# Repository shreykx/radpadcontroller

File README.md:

**radpad** - radpad is supposed to be a simple hackpad built on the radiation spider theme for [hackclub](https://hackclub.com) [#fallen](https://fallen.hackclub.com). the idea is, a macrocontroller that allows you to navigate your computer interface more easily than before. i will be documenting the progress on official fallout slack channel, and everything at source goes here :)

**for the reviewer**

**pcb schematic** - showing all the logical connections that will go into radpad's circuit. i've used in total three main electrical components, the com model joystick (it has both x and y directions plus a push button for center), four sw_switch for push buttons and a XIAO microcontroller.  

**pcb design** - i just connected the ratsnests to form a basic design, using both f.cu and b.cu layers making my board a 2 layered one.

3d front

3d back

i'm basically using the kicad's inbuilt 3d viewer to view how my board will look like at the end. which will decide if it works. i've also noted down the dimensions so the case is printed accordingly.

**3d model**

* software used: onshape

the base model is an imported one, which i will customize to fit radpad's theme. also there are a few layout shifts done.

i will upload more photos as i progress and also of the real ones after parts assembly.

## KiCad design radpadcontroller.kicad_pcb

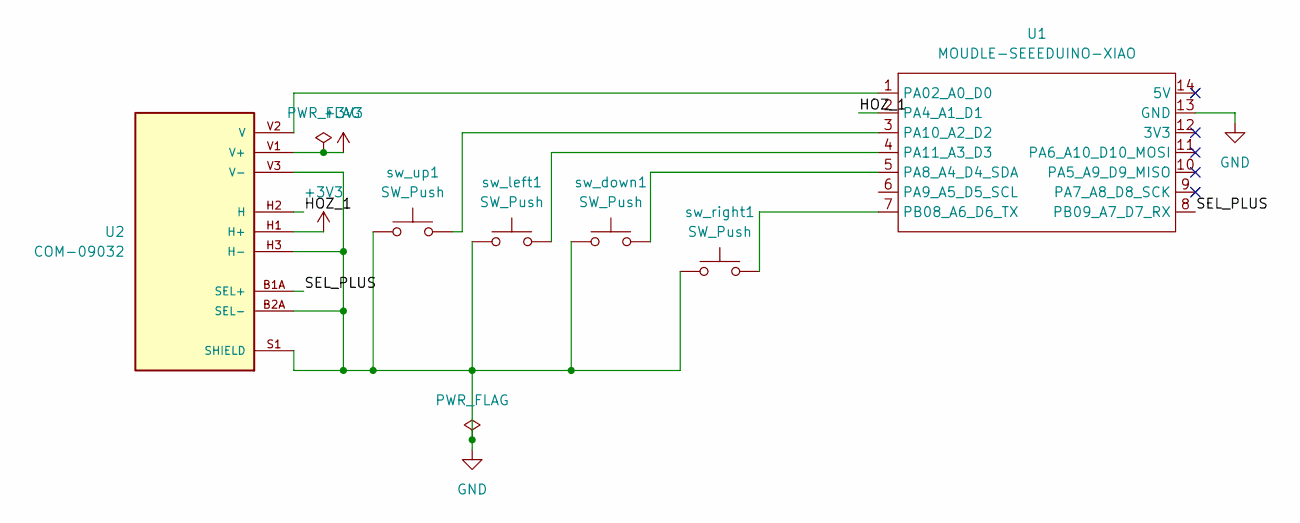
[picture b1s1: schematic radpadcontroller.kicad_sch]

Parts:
U1: MOUDLE-SEEEDUINO-XIAO; XIAO-Generic-Hybrid-14P-2.54-21X17.8MM
U2: COM-09032; XDCR_COM-09032; MPN COM-09032
sw_down1: SW_Push; SW_PUSH_6mm
sw_left1: SW_Push; SW_PUSH_6mm
sw_right1: SW_Push; SW_PUSH_6mm
sw_up1: SW_Push; SW_PUSH_6mm

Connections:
+3V3: U2.H1 (H+), U2.V1 (V+)
/HOZ_1: U1.2 (PA4_A1_D1), U2.H2 (H)
/SEL_PLUS: U1.8 (PB09_A7_D7_RX), U2.B1A (SEL+)
GND: U1.13 (GND), U2.B2A (SEL-), U2.H3 (H-), U2.S1 (SHIELD), U2.S2 (SHIELD), U2.S3 (SHIELD), U2.S4 (SHIELD), U2.V3 (V-), sw_down1.1, sw_left1.1, sw_right1.1, sw_up1.1
unnamed: U1.1 (PA02_A0_D0), U2.V2 (V)
unnamed: U1.5 (PA8_A4_D4_SDA), sw_down1.2
unnamed: U1.3 (PA10_A2_D2), sw_up1.2
unnamed: U1.4 (PA11_A3_D3), sw_left1.2
unnamed: U1.7 (PB08_A6_D6_TX), sw_right1.2

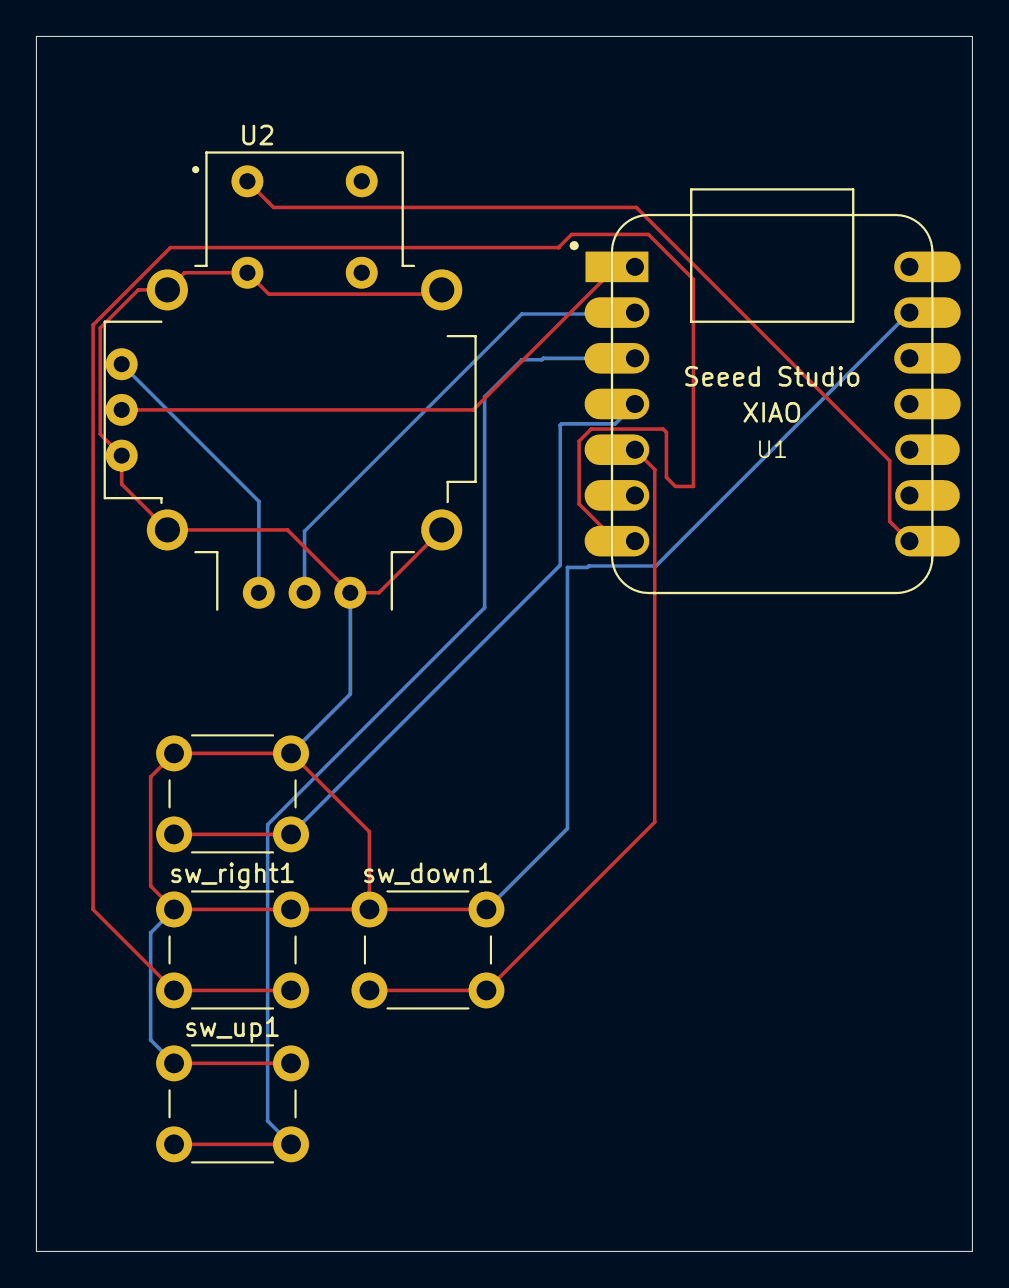
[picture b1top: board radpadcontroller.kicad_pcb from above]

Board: 2 copper layers, 52.0 x 67.5 mm, 6 parts (0 on the bottom side), 9 nets.
